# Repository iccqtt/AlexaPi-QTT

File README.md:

# AlexaPi-QTT
This repository contains a modified version of AlexaPi for the DragonBoard 410c optimized to work with Alexa Custom Skills and with AWS Lambda.

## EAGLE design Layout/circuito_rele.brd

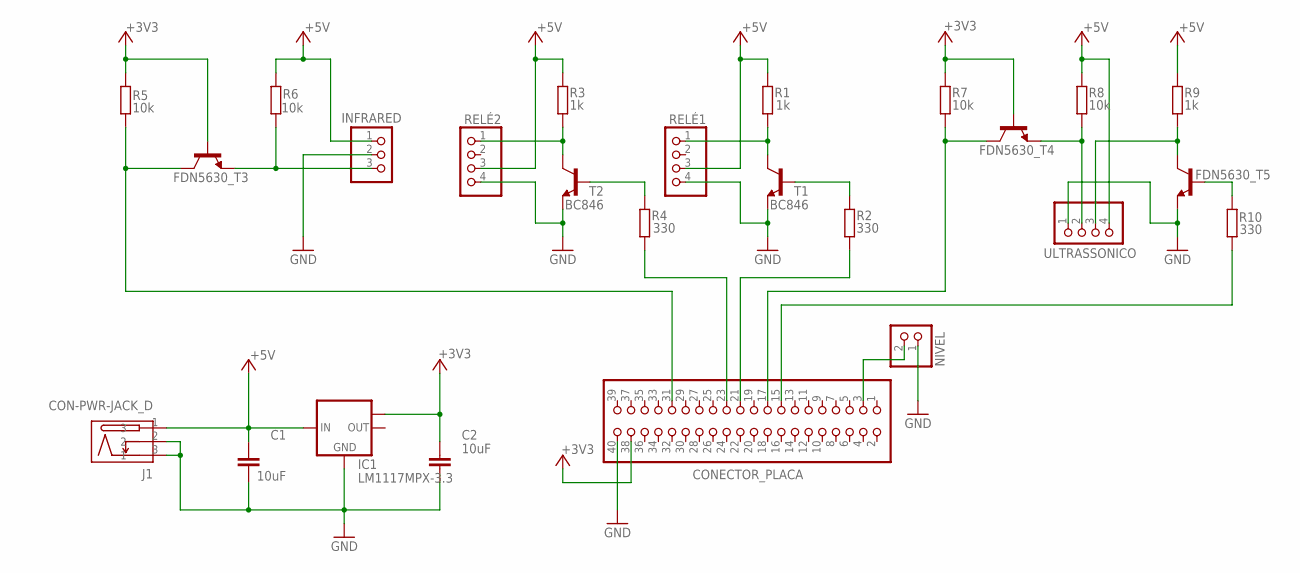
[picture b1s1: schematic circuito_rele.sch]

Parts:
C1, C2: 10uF; C4532
CONECTOR_PLACA: PINHD-2X20; 2X20
FDN5630_T3, FDN5630_T4, FDN5630_T5: BC846; SOT23
IC1: LM1117MPX-3.3; SOT223
INFRARED: PINHD-1X3; 1X03
J1: CON-PWR-JACK_D; TDC-002-3
NIVEL: PINHD-1X2; 1X02
R1, R3, R9: 1k; 0207/10
R2, R4, R10: 330; 0207/10
R5, R6, R7, R8: 10k; 0207/10
RELÉ1, RELÉ2: PINHD-1X4; 1X04
T1, T2: BC846; SOT23
ULTRASSONICO: PINHD-1X4; 1X04

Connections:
+3V3: C2.1, CONECTOR_PLACA.38, FDN5630_T3.1 (B), FDN5630_T4.1 (B), IC1.TAB (OUT1), R5.2, R7.1
+5V: C1.1, IC1.3 (IN), INFRARED.1, J1.1 (3), R1.1, R3.1, R6.2, R8.1, R9.1, RELÉ1.3, RELÉ2.3, ULTRASSONICO.4
GND: C1.2, C2.2, CONECTOR_PLACA.40, FDN5630_T5.2 (E), IC1.1 (GND), INFRARED.2, J1.2, J1.3 (1), NIVEL.1, RELÉ1.4, RELÉ2.4, T1.2 (E), T2.2 (E), ULTRASSONICO.1
unnamed: R1.2, RELÉ1.1, T1.3 (C)
unnamed: R4.1, T2.1 (B)
unnamed: CONECTOR_PLACA.23, R4.2
unnamed: R3.2, RELÉ2.1, T2.3 (C)
unnamed: R2.1, T1.1 (B)
unnamed: CONECTOR_PLACA.21, R2.2
unnamed: FDN5630_T3.2 (E), INFRARED.3, R6.1
unnamed: CONECTOR_PLACA.17, FDN5630_T4.3 (C), R7.2
unnamed: CONECTOR_PLACA.31, FDN5630_T3.3 (C), R5.1
unnamed: FDN5630_T5.3 (C), R9.2, ULTRASSONICO.3
unnamed: FDN5630_T4.2 (E), R8.2, ULTRASSONICO.2
unnamed: FDN5630_T5.1 (B), R10.2
unnamed: CONECTOR_PLACA.15, R10.1
unnamed: CONECTOR_PLACA.3, NIVEL.2

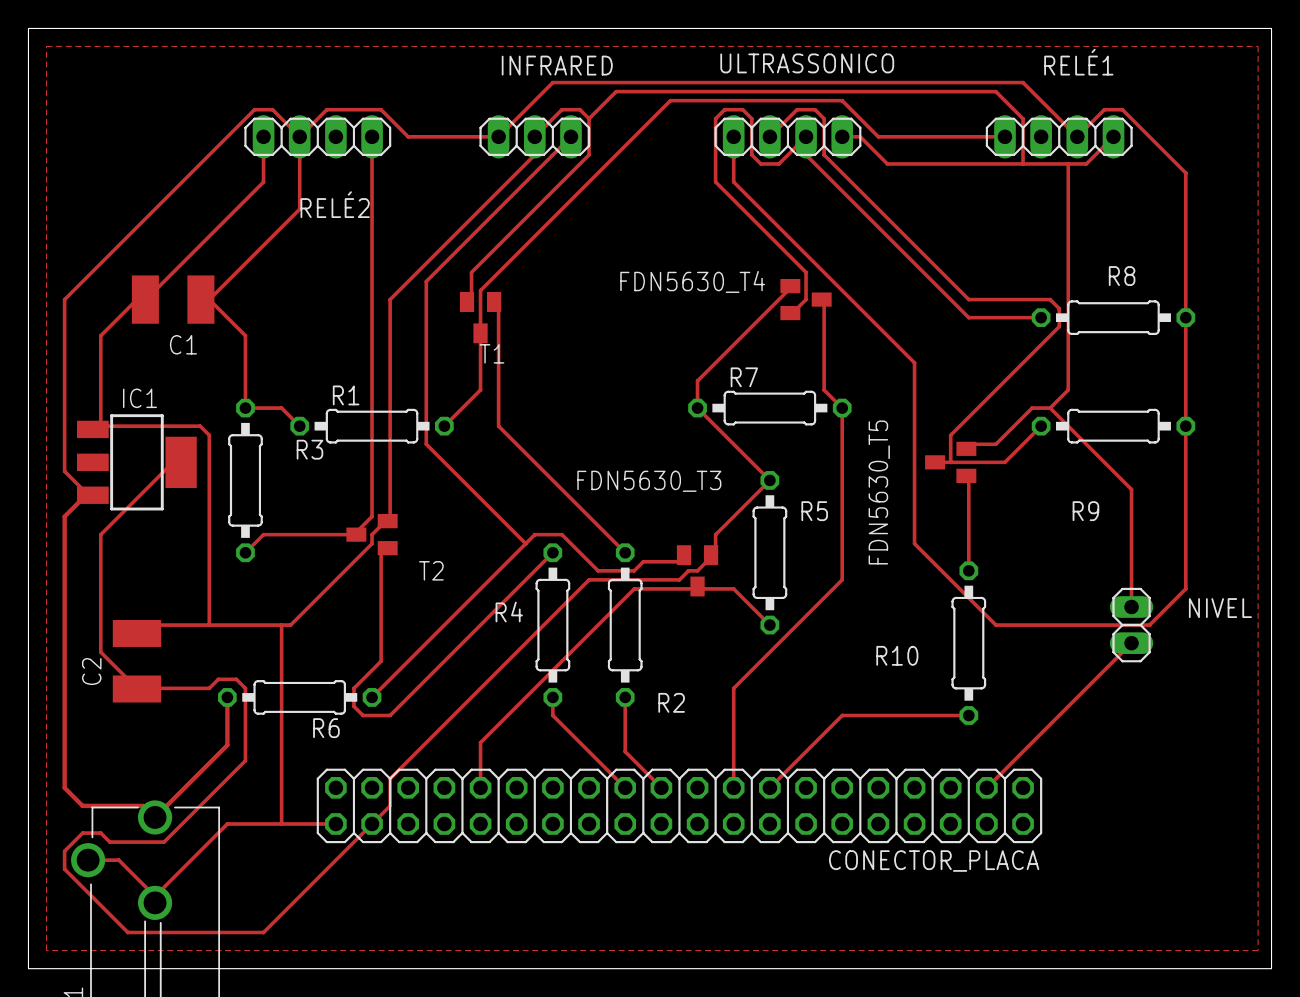
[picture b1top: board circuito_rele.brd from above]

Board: 2 copper layers, 87.3 x 66.0 mm, 25 parts (0 on the bottom side), 17 nets.

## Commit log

2018-09-06 Adding all files

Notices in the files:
parts and their libraries:
m-pad-2.1: License : GNU General Public License version 2 (see bottom)
